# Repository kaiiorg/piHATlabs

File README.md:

#PI HAT Labs
These are labs for a HAT originally designed as part of an independent study for Southeast Missouri State Universities' Department of Polytechnic Studies. It is designed for basic learning of Raspberry PI GPIO programming, using LEDs, switches, and a shift register with a seven segment display. The board also has additional headers on the various communications buses of the PI, to make it slightly easier to expand the hat while still using the components it supplies.

**_Snark Warning:_** If you think your students are special little snow flakes that need to be protected or take offense at every little thing, I suggest you don't bother reading the rest of this or consider deploying these labs to your students. I wrote these labs in a manner that I would have wanted: not boring or bland, with lots of useful information, with an occasional poke or prod to keep things interesting. This is written for _actual_ university level students. Freshman and sophomore level students, sure, but university students. Emailing me about the level of snark in these labs will only get you ignored.

##Instructors: Supply Your Students With These Materials:
1. A Raspberry Pi 2 or newer
2. A USB AC power adapter
3. An HDMI cable (or a cable that is HDMI -> whatever your lab's monitors support)
4. USB Mouse
5. USB Keyboard
6. Ethernet Cable
7. Network access to access these labs via web browser. Internet access required for some elements to load correctly.
8. Access to a Windows (7 to 10 should work) computer for the first lab, the other labs can be completed entirely on the PI.

##Lab 1: Install Rasbian on a Raspberry PI
Students learn to install the Rasbian OS onto a Raspberry PI. They will need access to a Windows computer for this part.
**_Instructors:_ Read the bottom of lab 1! You will need to manually download the Raspbian image and follow the directions there.**

##Lab 2: Test the HAT
Students learn about the physical layout of the HAT and run their first python program. This program tests all the components for functionality.

##Lab 3: GPIO Input and Output
Students learn basic electrical schematic elements and the electrical schematic of the HAT. They learn to turn the LEDs on or off and how that code works. They learn how to read input from the buttons and how that code works.

##Lab 4: Using a shift register
Students learn a little bit of binary, binary to decimal conversion, binary to hexidecimal conversion, how a shift register works, how to *use* a shift register

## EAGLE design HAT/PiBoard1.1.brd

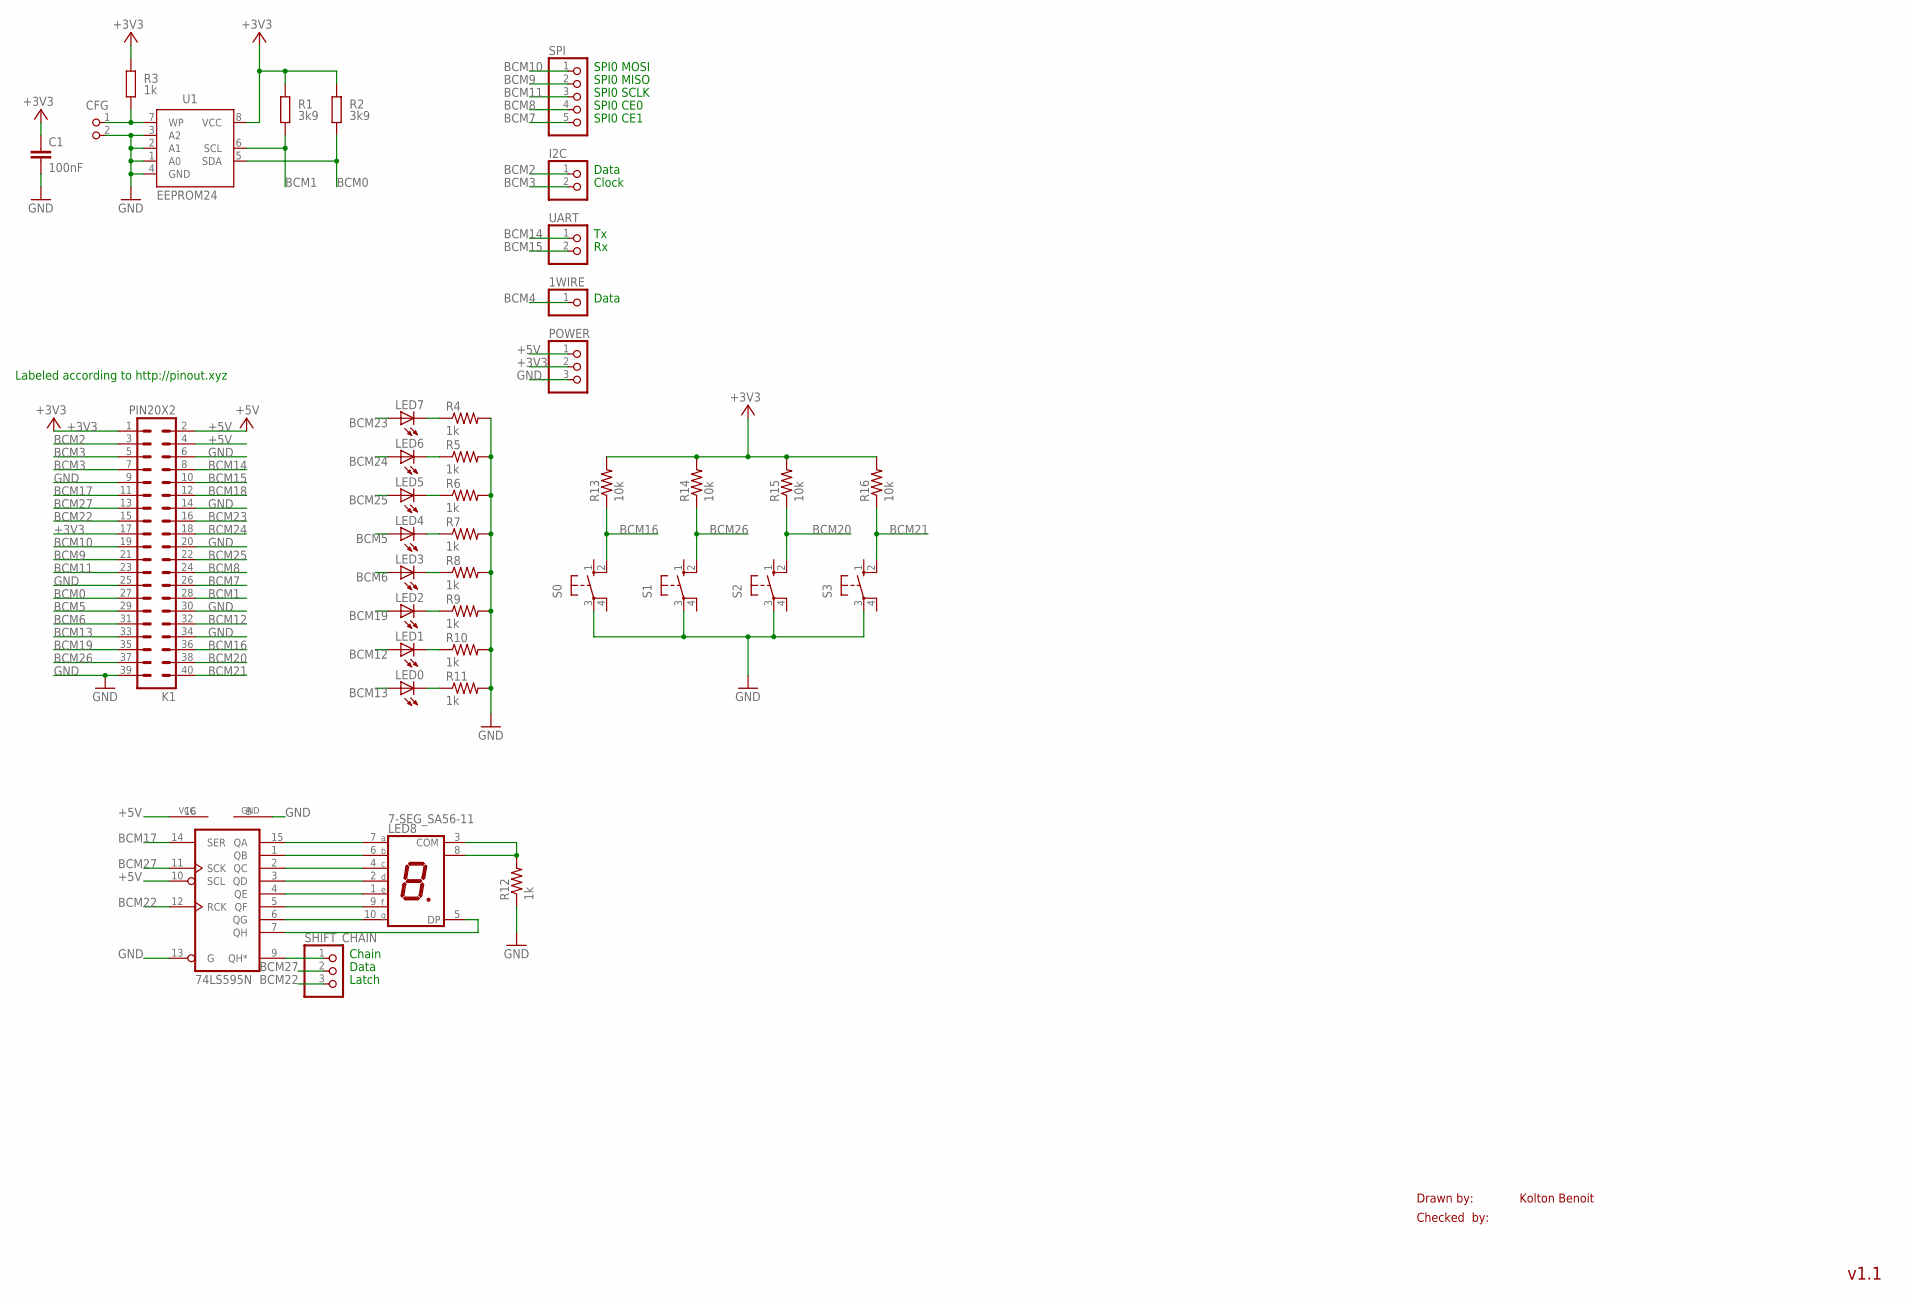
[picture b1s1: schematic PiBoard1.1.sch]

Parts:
1WIRE: PINHD-1X1; 1X01
C1: 100nF; C0805K
CFG: PIN2_100; PIN_W_2
I2C: PINHD-1X2; 1X02
K1: PIN20X2; PIN_20X2
LED0, LED1, LED2, LED3, LED4, LED5, LED6, LED7: LED3MM
LED8: 7-SEG_SA56-11; SA56-11
POWER: PINHD-1X3; 1X03
R1, R2: 3k9; M0805@1; TOLERANCE 5%
R3: 1k; M0805@1; TOLERANCE 5%
R4, R5, R6, R7, R8, R9, R10, R11, R12: 1k; 0204/7
R13, R14, R15, R16: 10k; 0204/7
S0, S1, S2, S3: 10-XX; B3F-10XX
SHIFT: 74LS595N; DIL16
SHIFT_CHAIN: PINHD-1X3; 1X03
SPI: PINHD-1X5; 1X05
U1: EEPROM24; SOIC8
UART: PINHD-1X2; 1X02

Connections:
+3V3: C1.1, K1.1, K1.17, POWER.2, R1.2, R2.2, R3.2, R13.2, R14.2, R15.2, R16.2, U1.8 (VCC)
+5V: K1.2, K1.4, POWER.1, SHIFT.10 (SCL), SHIFT.16 (VCC)
BCM0: K1.27, R2.1, U1.5 (SDA)
BCM1: K1.28, R1.1, U1.6 (SCL)
BCM2: I2C.1, K1.3
BCM3: I2C.2, K1.5
BCM4: 1WIRE.1, K1.7
BCM5: K1.29, LED4.A
BCM6: K1.31, LED3.A
BCM7: K1.26, SPI.5
BCM8: K1.24, SPI.4
BCM9: K1.21, SPI.2
BCM10: K1.19, SPI.1
BCM11: K1.23, SPI.3
BCM12: K1.32, LED1.A
BCM13: K1.33, LED0.A
BCM14: K1.8, UART.1
BCM15: K1.10, UART.2
BCM16: K1.36, R13.1, S0.2 (S1)
BCM17: K1.11, SHIFT.14 (SER)
BCM18: K1.12
BCM19: K1.35, LED2.A
BCM20: K1.38, R15.1, S2.2 (S1)
BCM21: K1.40, R16.1, S3.2 (S1)
BCM22: K1.15, SHIFT.12 (RCK), SHIFT_CHAIN.3
BCM23: K1.16, LED7.A
BCM24: K1.18, LED6.A
BCM25: K1.22, LED5.A
BCM26: K1.37, R14.1, S1.2 (S1)
BCM27: K1.13, SHIFT.11 (SCK), SHIFT_CHAIN.2
GND: C1.2, CFG.2, K1.6, K1.9, K1.14, K1.20, K1.25, K1.30, K1.34, K1.39, POWER.3, R4.2, R5.2, R6.2, R7.2, R8.2, R9.2, R10.2, R11.2, R12.1, S0.3, S1.3, S2.3, S3.3, SHIFT.8 (GND), SHIFT.13 (G), U1.1 (A0), U1.2 (A1), U1.3 (A2), U1.4 (GND)
unnamed: CFG.1, R3.1, U1.7 (WP)
unnamed: LED8.7 (A), SHIFT.15 (QA)
unnamed: LED8.6 (B), SHIFT.1 (QB)
unnamed: LED8.4 (C), SHIFT.2 (QC)
unnamed: LED8.2 (D), SHIFT.3 (QD)
unnamed: LED8.1 (E), SHIFT.4 (QE)
unnamed: LED8.9 (F), SHIFT.5 (QF)
unnamed: LED8.10 (G), SHIFT.6 (QG)
unnamed: LED8.5 (DP), SHIFT.7 (QH)
unnamed: LED0.K (C), R11.1
unnamed: LED1.K (C), R10.1
unnamed: LED2.K (C), R9.1
unnamed: LED3.K (C), R8.1
unnamed: LED4.K (C), R7.1
unnamed: LED5.K (C), R6.1
unnamed: LED6.K (C), R5.1
unnamed: LED7.K (C), R4.1
unnamed: SHIFT.9 (QH*), SHIFT_CHAIN.1
unnamed: LED8.3 (COM), LED8.8 (COM), R12.2

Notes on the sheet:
Drawn by:
Checked by:
Kolton Benoit
v1.1
SPI0 MOSI
SPI0 MISO
SPI0 SCLK
SPI0 CE0
SPI0 CE1
Data
Clock
Chain
Latch
Labeled according to http://pinout.xyz

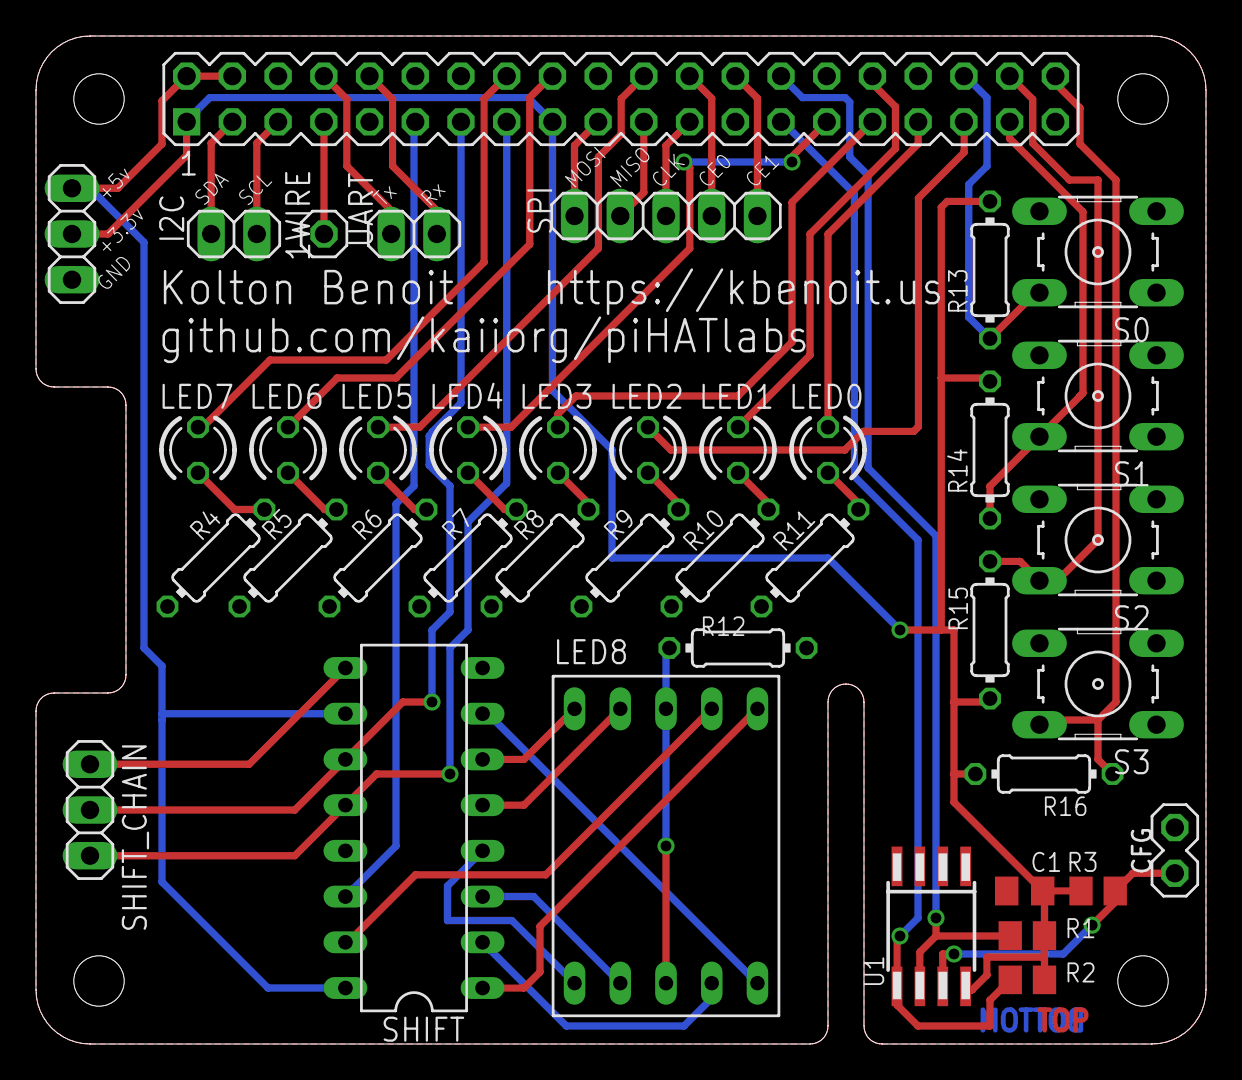
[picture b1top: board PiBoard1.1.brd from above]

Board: 2 copper layers, 65.0 x 56.0 mm, 40 parts (0 on the bottom side), 49 nets.

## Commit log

2017-03-05 Inital commit
2017-03-05 3 labs and images for them
2017-03-05 Stubs for labs 4, 5, 6, 7
2017-03-05 Fixed bug in leds.py. Made progress on lab 4
2017-03-06 More progress on lab 4
2017-03-09 Lab 4: Bitwise operations and functions explained
2017-03-10 Finished lab 4. Nuked labs 5, 6, 7; I think they're a little too complex to do without an actual lecture.
2017-03-21 Added the HAT's source files
2017-03-29 Fixed label in board schematic
2017-03-29 Changed a few pictures, fixed spelling mistakes, added nav arrows
2017-03-29 basic bash script for hosting the labs with the python http server
2017-04-05 Changed the placeholder name with an actual name
2017-04-18 Changed the test script's wording. Hopefully fixed the bug in button.py. Still need to add instructions for changing keyboard country
2017-04-20 Downloaded all .css and .js files needed to display the labs.An internet connection shouldn't be required anymore.
2017-04-25 Fixed links
2021-03-16 Fixed css/js/etc not loading on front page when loading from disk
